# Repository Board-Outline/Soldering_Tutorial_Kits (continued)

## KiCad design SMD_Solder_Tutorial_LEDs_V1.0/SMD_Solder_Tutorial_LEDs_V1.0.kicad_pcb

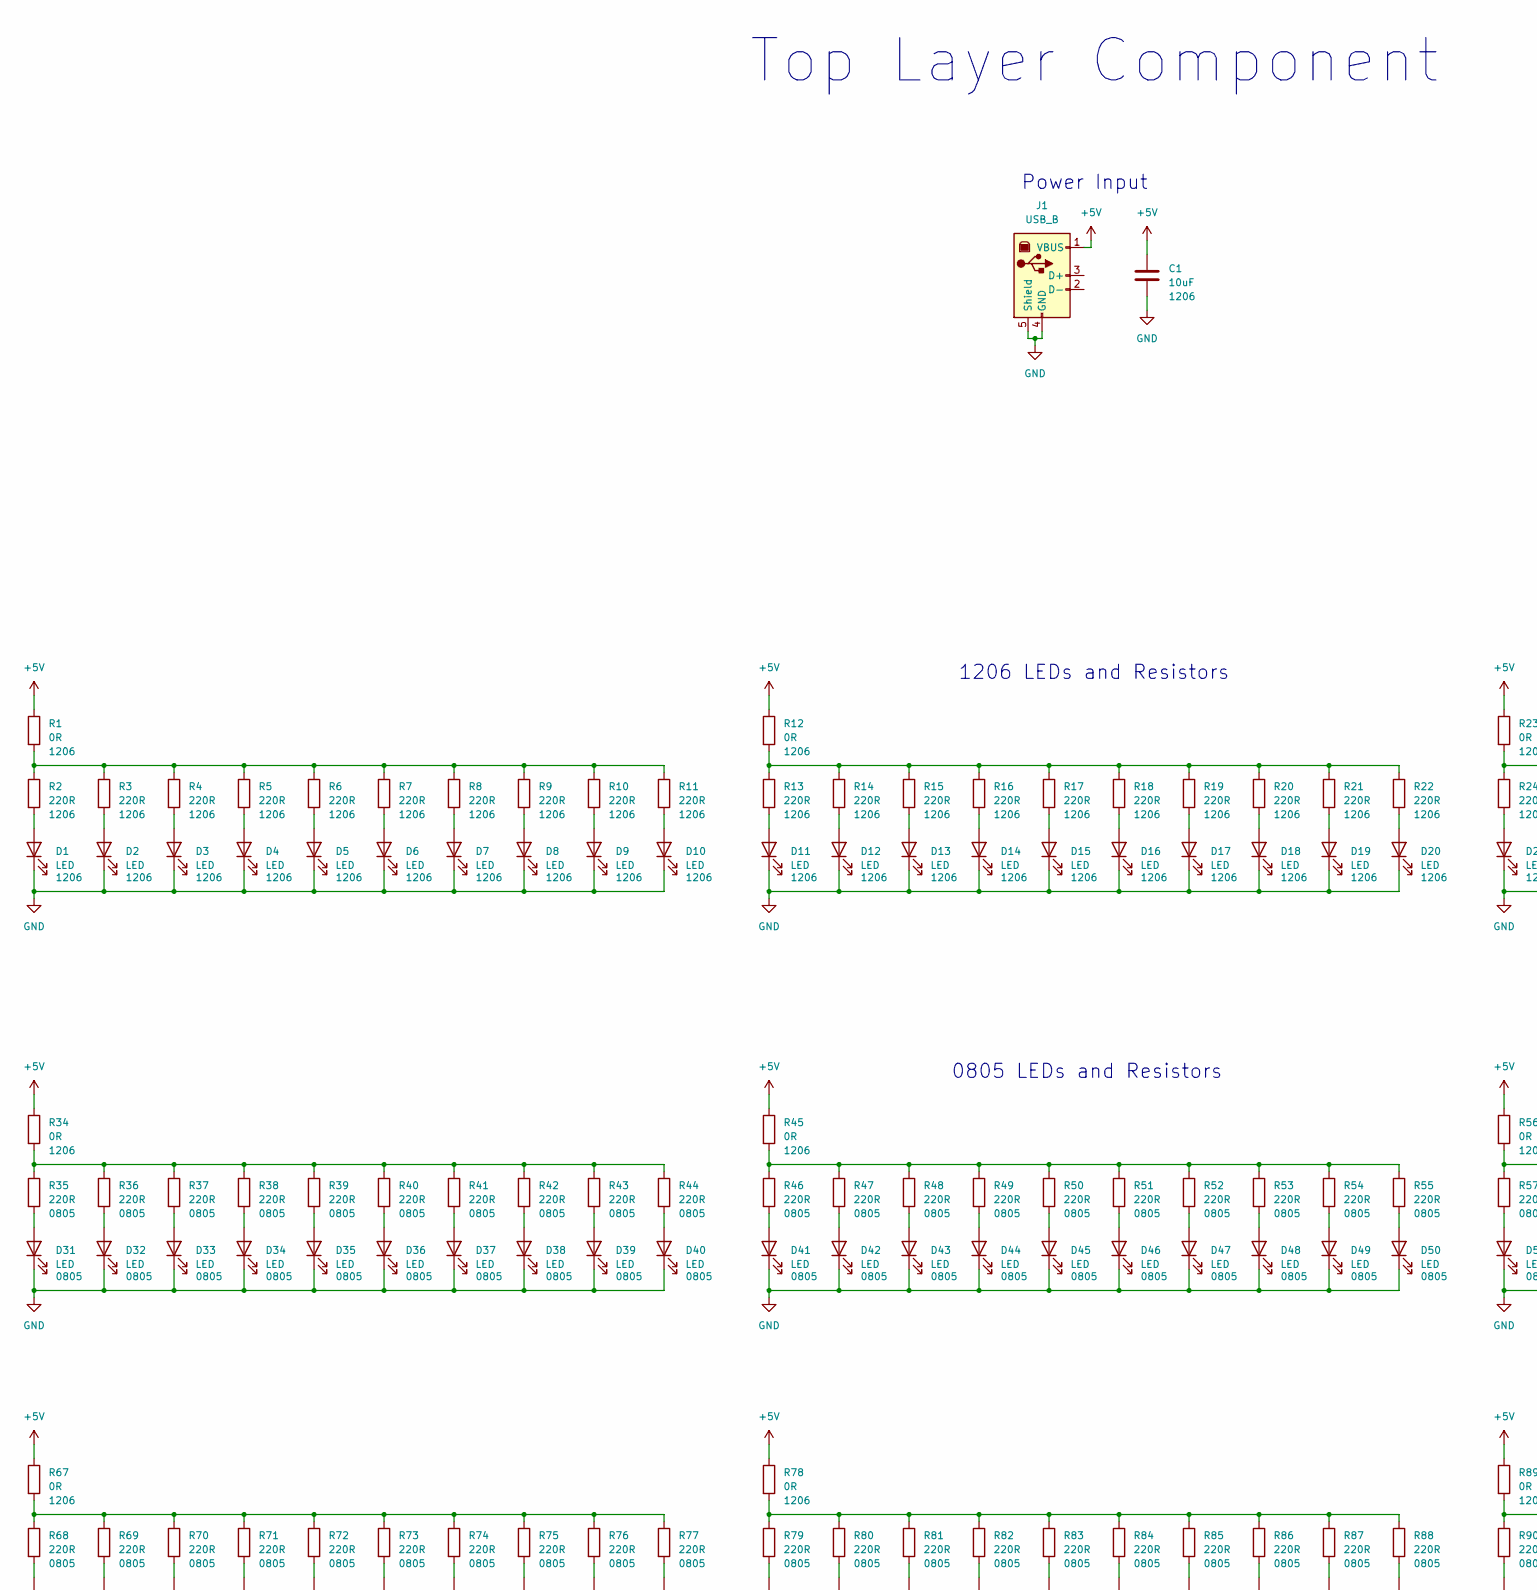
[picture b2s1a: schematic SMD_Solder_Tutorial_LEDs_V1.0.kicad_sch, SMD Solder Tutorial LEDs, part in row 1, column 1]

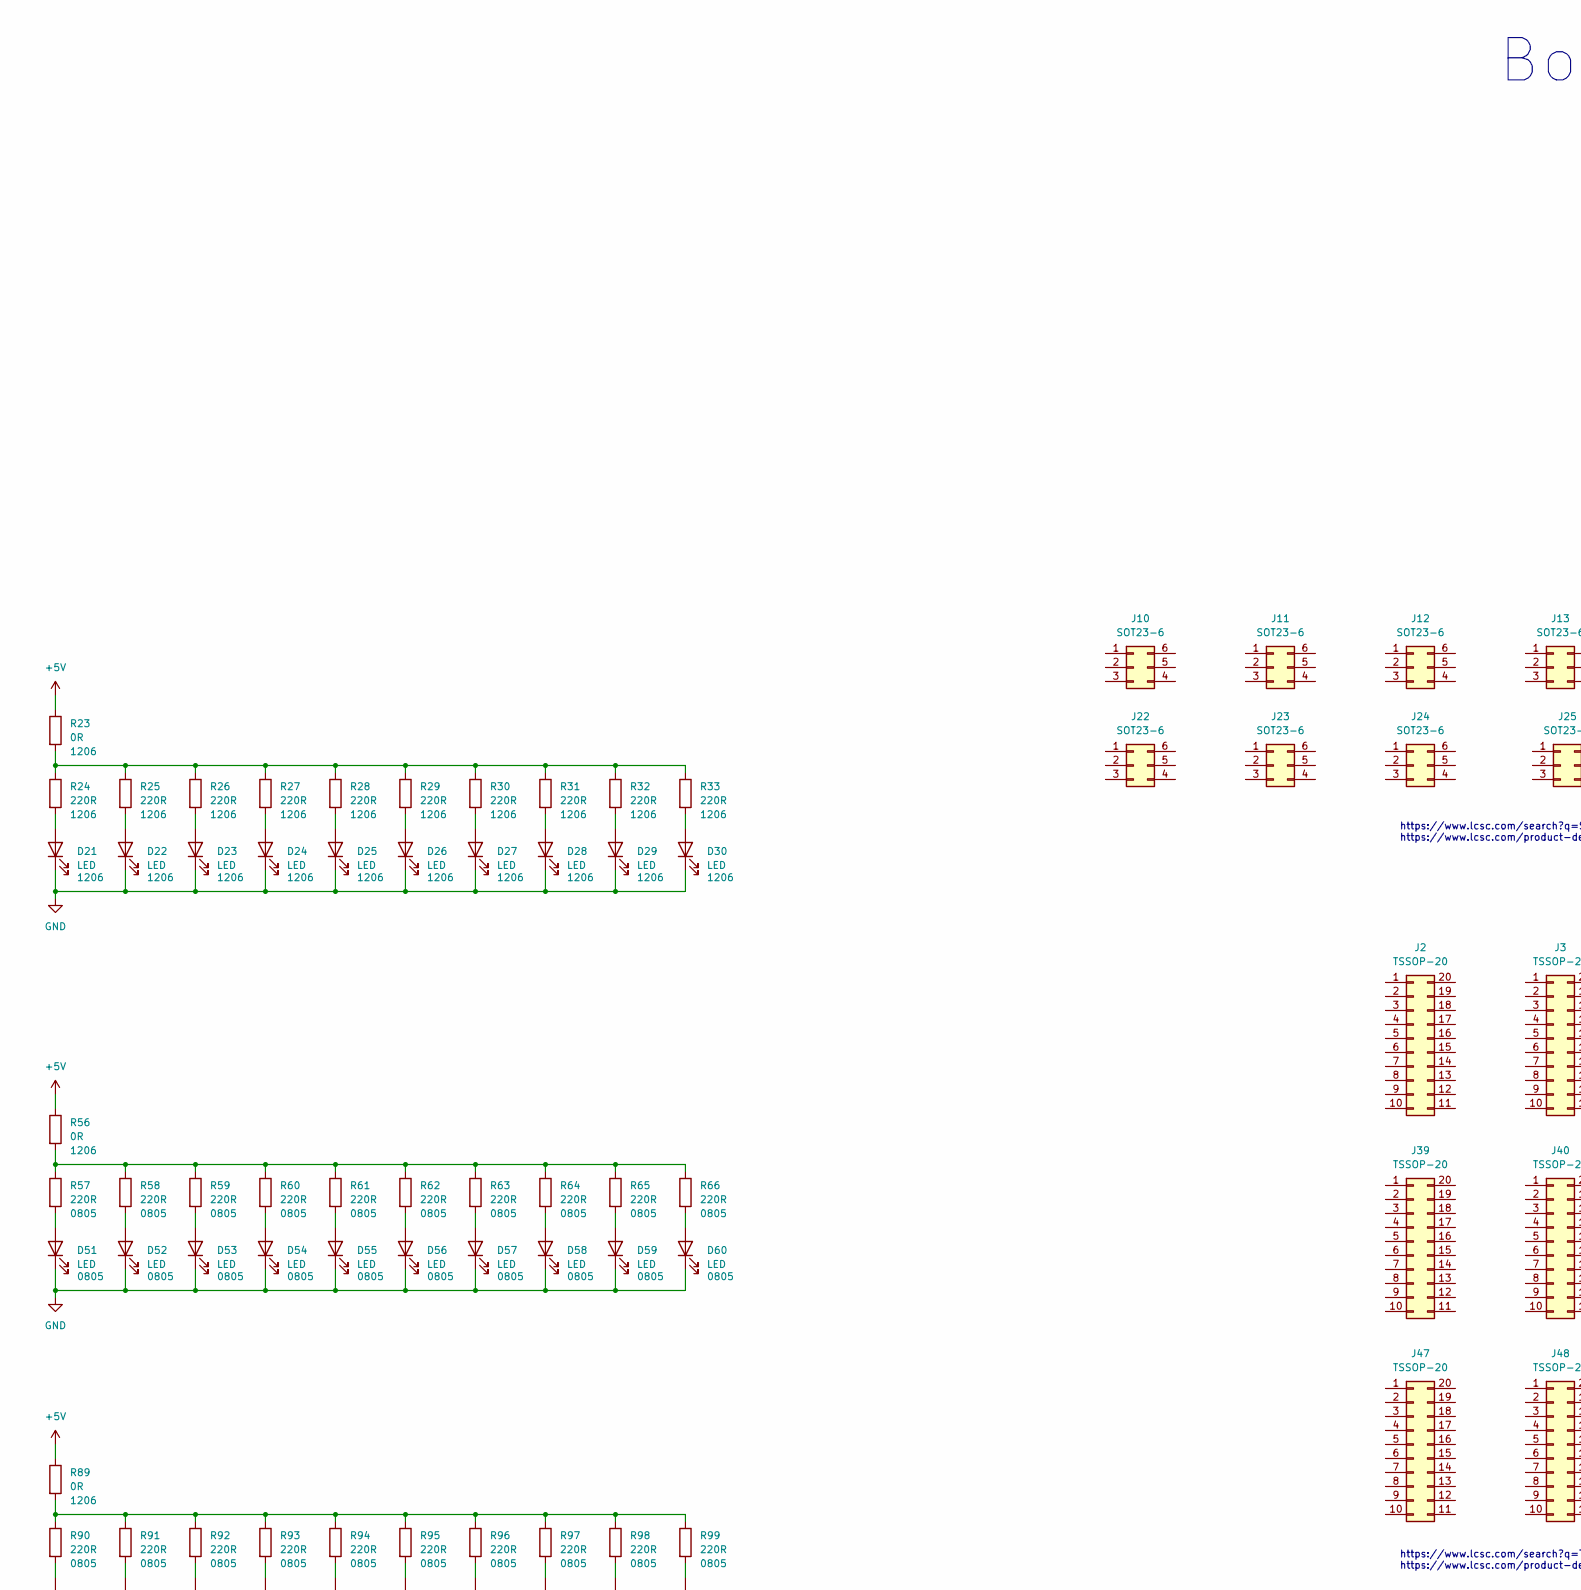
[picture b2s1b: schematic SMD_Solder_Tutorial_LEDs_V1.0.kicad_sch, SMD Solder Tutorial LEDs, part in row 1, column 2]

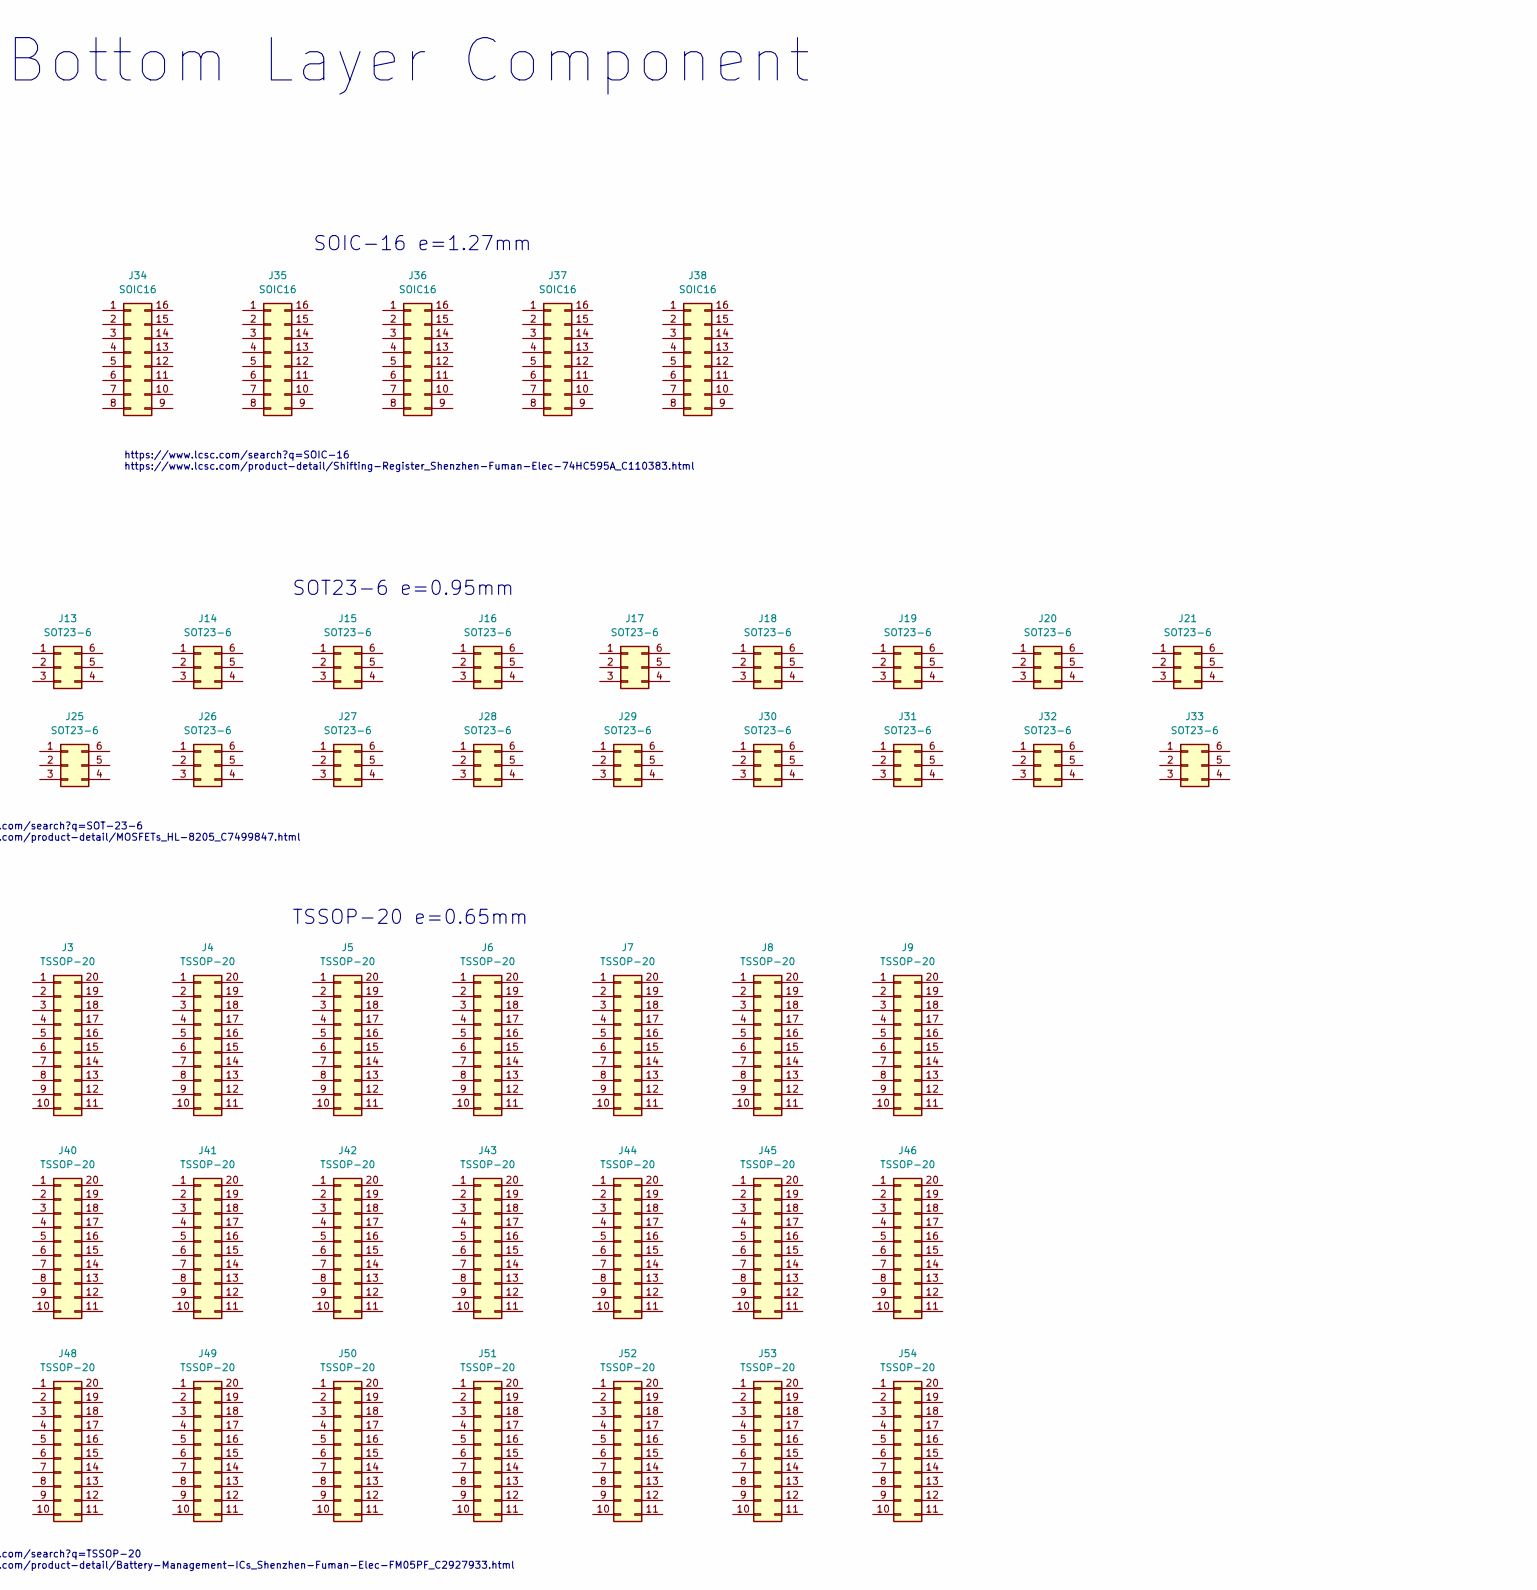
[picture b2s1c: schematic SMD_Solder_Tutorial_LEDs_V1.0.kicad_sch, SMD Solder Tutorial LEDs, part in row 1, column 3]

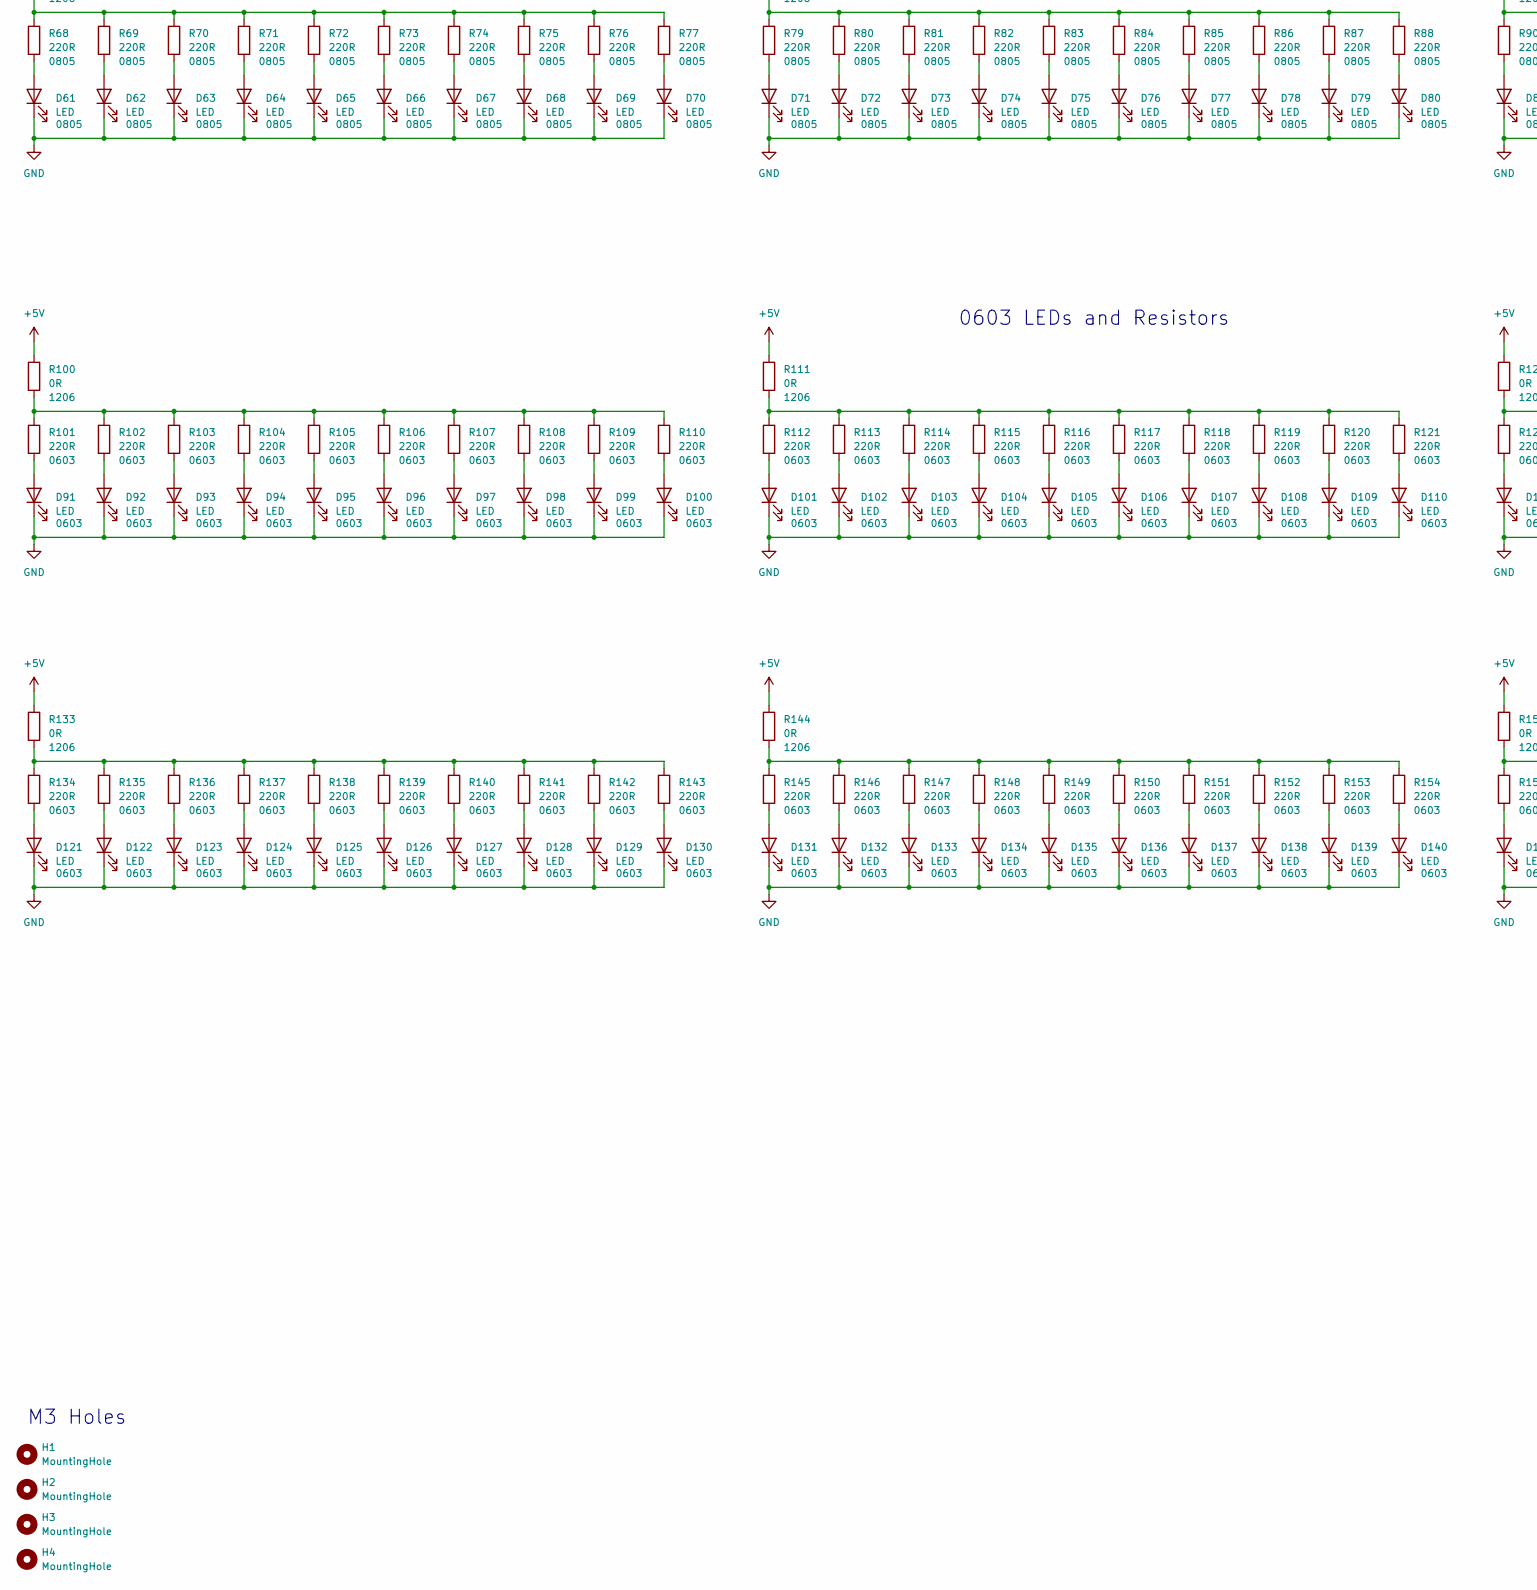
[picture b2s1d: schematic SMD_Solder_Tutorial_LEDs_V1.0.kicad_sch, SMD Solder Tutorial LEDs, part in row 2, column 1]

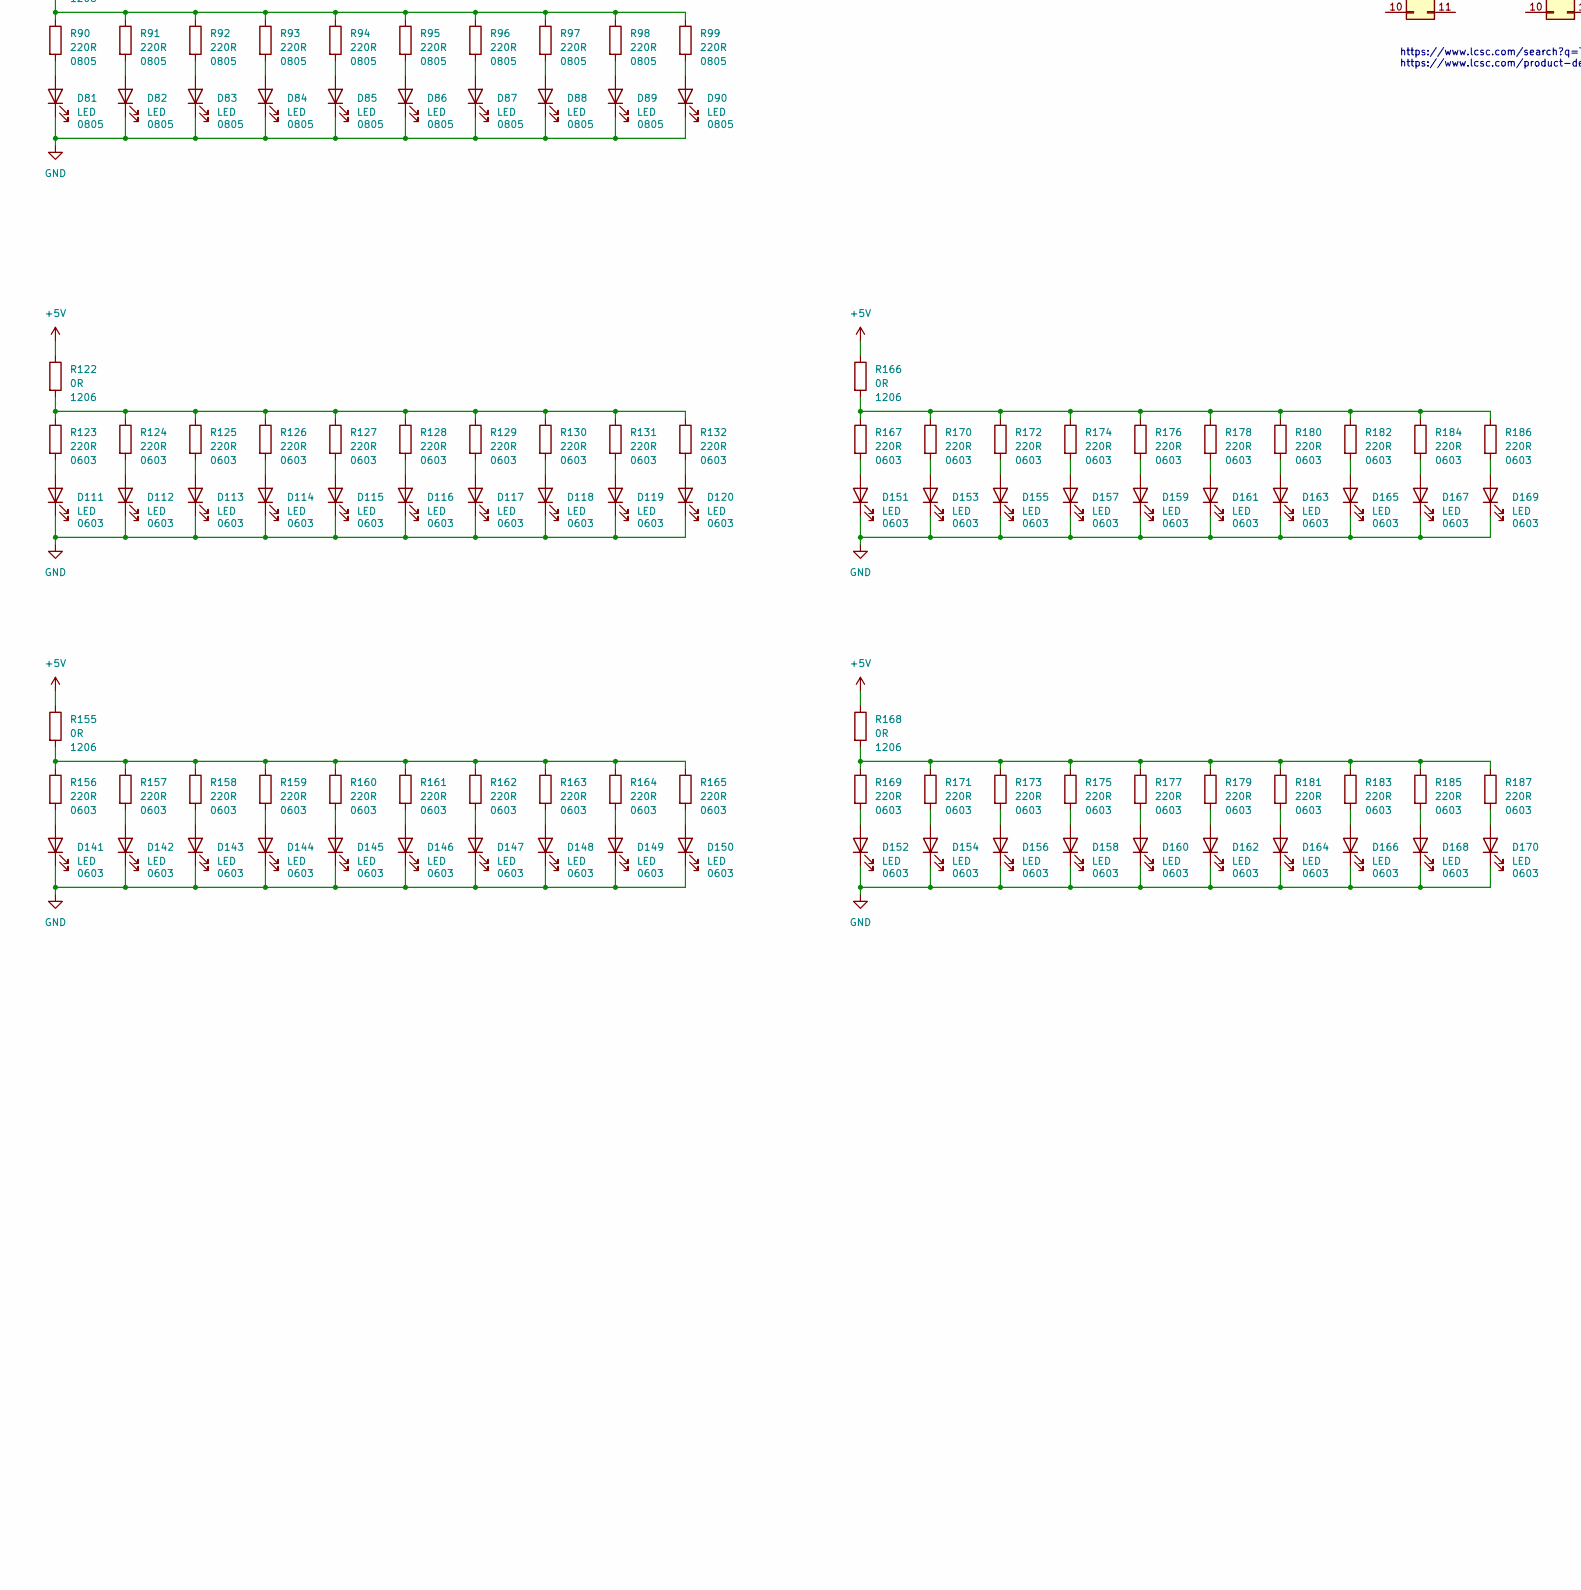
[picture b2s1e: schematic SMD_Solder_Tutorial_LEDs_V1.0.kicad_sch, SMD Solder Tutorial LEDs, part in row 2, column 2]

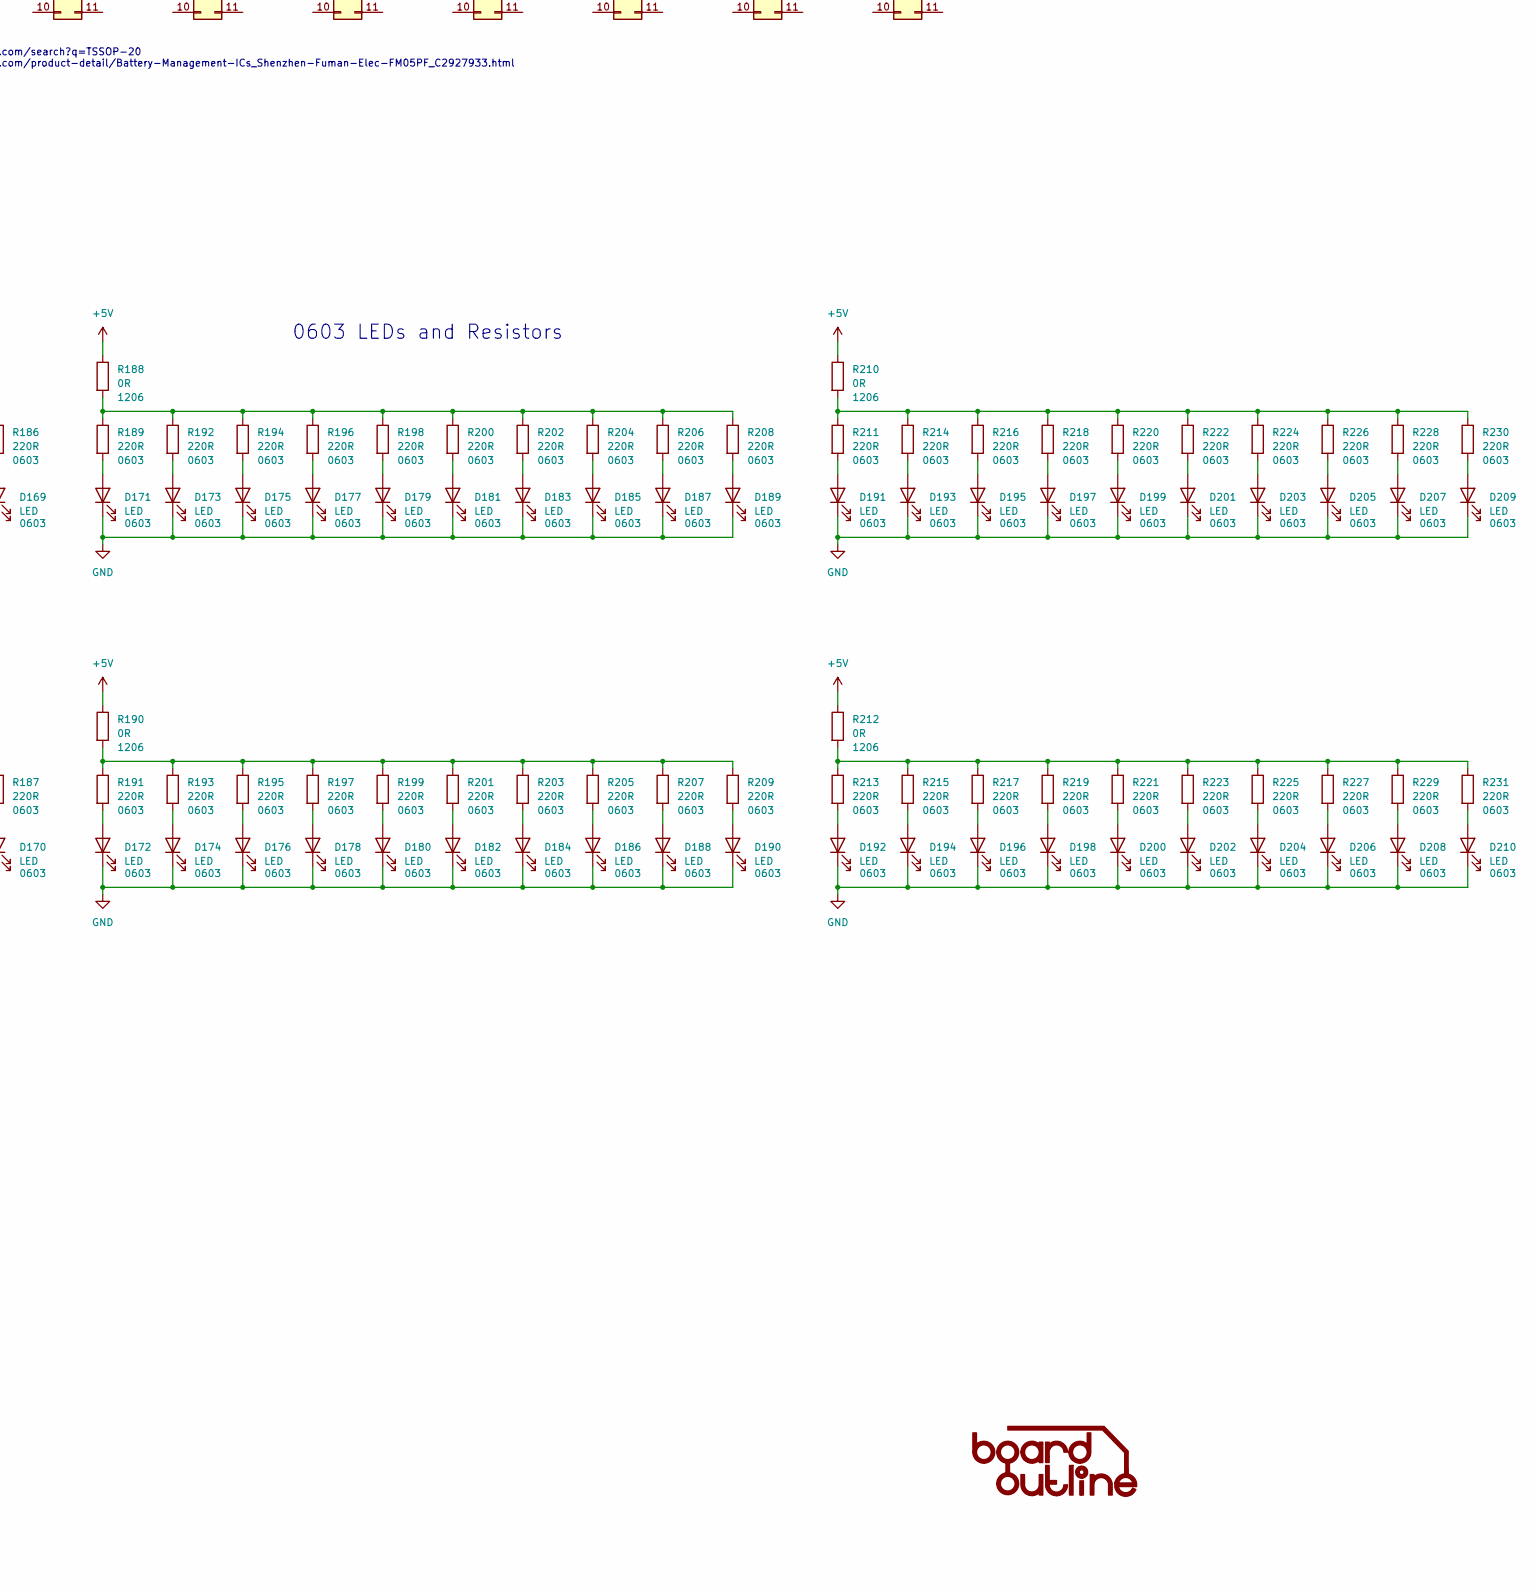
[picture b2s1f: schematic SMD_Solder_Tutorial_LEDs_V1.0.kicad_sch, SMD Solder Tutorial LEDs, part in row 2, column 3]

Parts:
C1: 10uF; C_1206_3216Metric_Pad1.33x1.80mm_HandSolder
D1, D2, D3, D4, D5, D6, D7, D8, D9, D10, D11, D12, D13, D14, D15, D16, D17, D18, D19, D20, D21, D22, D23, D24, D25, D26, D27, D28, D29, D30: LED; LED_1206_3216Metric_Pad1.42x1.75mm_HandSolder; Manufacturer Part Number XL-3216UGC
D31, D32, D33, D34, D35, D36, D37, D38, D39, D40, D41, D42, D43, D44, D45, D46, D47, D48, D49, D50, D51, D52, D53, D54, D55, D56, D57, D58, D59, D60, D61, D62, D63, D64, D65, D66, D67, D68, D69, D70, D71, D72, D73, D74, D75, D76, D77, D78, D79, D80, D81, D82, D83, D84, D85, D86, D87, D88, D89, D90: LED; LED_0805_2012Metric_Pad1.15x1.40mm_HandSolder; Manufacturer Part Number XL-2012UGC
D91, D92, D93, D94, D95, D96, D97, D98, D99, D100, D101, D102, D103, D104, D105, D106, D107, D108, D109, D110, D111, D112, D113, D114, D115, D116, D117, D118, D119, D120, D121, D122, D123, D124, D125, D126, D127, D128, D129, D130, D131, D132, D133, D134, D135, D136, D137, D138, D139, D140, D141, D142, D143, D144, D145, D146, D147, D148, D149, D150, D151, D152, D153, D154, D155, D156, D157, D158, D159, D160, D161, D162, D163, D164, D165, D166, D167, D168, D169, D170, D171, D172, D173, D174, D175, D176, D177, D178, D179, D180, D181, D182, D183, D184, D185, D186, D187, D188, D189, D190, D191, D192, D193, D194, D195, D196, D197, D198, D199, D200, D201, D202, D203, D204, D205, D206, D207, D208, D209, D210: LED; LED_0603_1608Metric_Pad1.05x0.95mm_HandSolder; Manufacturer Part Number XL-1608UGC-04
H1, H2, H3, H4: MountingHole; MountingHole_3.2mm_M3_DIN965
J1: USB_B; USB_B_OST_USB-B1HSxx_Horizontal; Manufacturer Part Number USB-B10-BRW
J2, J3, J4, J5, J6, J7, J8, J9, J39, J40, J41, J42, J43, J44, J45, J46, J47, J48, J49, J50, J51, J52, J53, J54: TSSOP-20; TSSOP-20_4.4x6.5mm_P0.65mm; Manufacturer Part Number FM05PF
J10, J11, J12, J13, J14, J15, J16, J17, J18, J19, J20, J21, J22, J23, J24, J25, J26, J27, J28, J29, J30, J31, J32, J33: SOT23-6; SOT-23-6_Handsoldering
J34, J35, J36, J37, J38: SOIC16; SOIC-16W_5.3x10.2mm_P1.27mm; Manufacturer Part Number C7499847
R1, R12, R23, R34, R45, R56, R67, R78, R89, R100, R111, R122, R133, R144, R155, R166, R168, R188, R190, R210, R212: 0R; R_1206_3216Metric_Pad1.30x1.75mm_HandSolder
R2, R3, R4, R5, R6, R7, R8, R9, R10, R11, R13, R14, R15, R16, R17, R18, R19, R20, R21, R22, R24, R25, R26, R27, R28, R29, R30, R31, R32, R33: 220R; R_1206_3216Metric_Pad1.30x1.75mm_HandSolder
R35, R36, R37, R38, R39, R40, R41, R42, R43, R44, R46, R47, R48, R49, R50, R51, R52, R53, R54, R55, R57, R58, R59, R60, R61, R62, R63, R64, R65, R66, R68, R69, R70, R71, R72, R73, R74, R75, R76, R77, R79, R80, R81, R82, R83, R84, R85, R86, R87, R88, R90, R91, R92, R93, R94, R95, R96, R97, R98, R99: 220R; R_0805_2012Metric_Pad1.20x1.40mm_HandSolder
R101, R102, R103, R104, R105, R106, R107, R108, R109, R110, R112, R113, R114, R115, R116, R117, R118, R119, R120, R121, R123, R124, R125, R126, R127, R128, R129, R130, R131, R132, R134, R135, R136, R137, R138, R139, R140, R141, R142, R143, R145, R146, R147, R148, R149, R150, R151, R152, R153, R154, R156, R157, R158, R159, R160, R161, R162, R163, R164, R165, R167, R169, R170, R171, R172, R173, R174, R175, R176, R177, R178, R179, R180, R181, R182, R183, R184, R185, R186, R187, R189, R191, R192, R193, R194, R195, R196, R197, R198, R199, R200, R201, R202, R203, R204, R205, R206, R207, R208, R209, R211, R213, R214, R215, R216, R217, R218, R219, R220, R221, R222, R223, R224, R225, R226, R227, R228, R229, R230, R231: 220R; R_0603_1608Metric_Pad0.98x0.95mm_HandSolder

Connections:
+5V: C1.1, J1.1 (VBUS), R1.1, R12.1, R23.1, R34.1, R45.1, R56.1, R67.1, R78.1, R89.1, R100.1, R111.1, R122.1, R133.1, R144.1, R155.1, R166.1, R168.1, R188.1, R190.1, R210.1, R212.1
GND: C1.2, D1.1 (K), D2.1 (K), D3.1 (K), D4.1 (K), D5.1 (K), D6.1 (K), D7.1 (K), D8.1 (K), D9.1 (K), D10.1 (K), D11.1 (K), D12.1 (K), D13.1 (K), D14.1 (K), D15.1 (K), D16.1 (K), D17.1 (K), D18.1 (K), D19.1 (K), D20.1 (K), D21.1 (K), D22.1 (K), D23.1 (K), D24.1 (K), D25.1 (K), D26.1 (K), D27.1 (K), D28.1 (K), D29.1 (K), D30.1 (K), D31.1 (K), D32.1 (K), D33.1 (K), D34.1 (K), D35.1 (K), D36.1 (K), D37.1 (K), D38.1 (K), D39.1 (K), D40.1 (K), D41.1 (K), D42.1 (K), D43.1 (K), D44.1 (K), D45.1 (K), D46.1 (K), D47.1 (K), D48.1 (K), D49.1 (K), D50.1 (K), D51.1 (K), D52.1 (K), D53.1 (K), D54.1 (K), D55.1 (K), D56.1 (K), D57.1 (K), D58.1 (K), D59.1 (K), D60.1 (K), D61.1 (K), D62.1 (K), D63.1 (K), D64.1 (K), D65.1 (K), D66.1 (K), D67.1 (K), D68.1 (K), D69.1 (K), D70.1 (K), D71.1 (K), D72.1 (K), D73.1 (K), D74.1 (K), D75.1 (K), D76.1 (K), D77.1 (K), D78.1 (K), D79.1 (K), D80.1 (K), D81.1 (K), D82.1 (K), D83.1 (K), D84.1 (K), D85.1 (K), D86.1 (K), D87.1 (K), D88.1 (K), D89.1 (K), D90.1 (K), D91.1 (K), D92.1 (K), D93.1 (K), D94.1 (K), D95.1 (K), D96.1 (K), D97.1 (K), D98.1 (K), D99.1 (K), D100.1 (K), D101.1 (K), D102.1 (K), D103.1 (K), D104.1 (K), D105.1 (K), D106.1 (K), D107.1 (K), D108.1 (K), D109.1 (K), D110.1 (K), D111.1 (K), D112.1 (K), D113.1 (K), D114.1 (K), D115.1 (K), D116.1 (K), D117.1 (K), D118.1 (K), D119.1 (K), D120.1 (K), D121.1 (K), D122.1 (K), D123.1 (K), D124.1 (K), D125.1 (K), D126.1 (K), D127.1 (K), D128.1 (K), D129.1 (K), D130.1 (K), D131.1 (K), D132.1 (K), D133.1 (K), D134.1 (K), D135.1 (K), D136.1 (K), D137.1 (K), D138.1 (K), D139.1 (K), D140.1 (K), D141.1 (K), D142.1 (K), D143.1 (K), D144.1 (K), D145.1 (K), D146.1 (K), D147.1 (K), D148.1 (K), D149.1 (K), D150.1 (K), D151.1 (K), D152.1 (K), D153.1 (K), D154.1 (K), D155.1 (K), D156.1 (K), D157.1 (K), D158.1 (K), D159.1 (K), D160.1 (K), D161.1 (K), D162.1 (K), D163.1 (K), D164.1 (K), D165.1 (K), D166.1 (K), D167.1 (K), D168.1 (K), D169.1 (K), D170.1 (K), D171.1 (K), D172.1 (K), D173.1 (K), D174.1 (K), D175.1 (K), D176.1 (K), D177.1 (K), D178.1 (K), D179.1 (K), D180.1 (K), D181.1 (K), D182.1 (K), D183.1 (K), D184.1 (K), D185.1 (K), D186.1 (K), D187.1 (K), D188.1 (K), D189.1 (K), D190.1 (K), D191.1 (K), D192.1 (K), D193.1 (K), D194.1 (K), D195.1 (K), D196.1 (K), D197.1 (K), D198.1 (K), D199.1 (K), D200.1 (K), D201.1 (K), D202.1 (K), D203.1 (K), D204.1 (K), D205.1 (K), D206.1 (K), D207.1 (K), D208.1 (K), D209.1 (K), D210.1 (K), J1.4 (GND), J1.5 (Shield)
unnamed: D1.2 (A), R2.2
unnamed: D2.2 (A), R3.2
unnamed: D3.2 (A), R4.2
unnamed: D4.2 (A), R5.2
unnamed: D5.2 (A), R6.2
unnamed: D6.2 (A), R7.2
unnamed: D7.2 (A), R8.2
unnamed: D8.2 (A), R9.2
unnamed: D9.2 (A), R10.2
unnamed: D10.2 (A), R11.2
unnamed: D11.2 (A), R13.2
unnamed: D12.2 (A), R14.2
unnamed: D13.2 (A), R15.2
unnamed: D14.2 (A), R16.2
unnamed: D15.2 (A), R17.2
unnamed: D16.2 (A), R18.2
unnamed: D17.2 (A), R19.2
unnamed: D18.2 (A), R20.2
unnamed: D19.2 (A), R21.2
unnamed: D20.2 (A), R22.2
unnamed: D21.2 (A), R24.2
unnamed: D22.2 (A), R25.2
unnamed: D23.2 (A), R26.2
unnamed: D24.2 (A), R27.2
unnamed: D25.2 (A), R28.2
unnamed: D26.2 (A), R29.2
unnamed: D27.2 (A), R30.2
unnamed: D28.2 (A), R31.2
unnamed: D29.2 (A), R32.2
unnamed: D30.2 (A), R33.2
unnamed: D31.2 (A), R35.2
unnamed: D32.2 (A), R36.2
unnamed: D33.2 (A), R37.2
unnamed: D34.2 (A), R38.2
unnamed: D35.2 (A), R39.2
unnamed: D36.2 (A), R40.2
unnamed: D37.2 (A), R41.2
unnamed: D38.2 (A), R42.2
unnamed: D39.2 (A), R43.2
unnamed: D40.2 (A), R44.2
unnamed: D41.2 (A), R46.2
unnamed: D42.2 (A), R47.2
unnamed: D43.2 (A), R48.2
unnamed: D44.2 (A), R49.2
unnamed: D45.2 (A), R50.2
unnamed: D46.2 (A), R51.2
unnamed: D47.2 (A), R52.2
unnamed: D48.2 (A), R53.2
unnamed: D49.2 (A), R54.2
unnamed: D50.2 (A), R55.2
unnamed: D51.2 (A), R57.2
unnamed: D52.2 (A), R58.2
unnamed: D53.2 (A), R59.2
unnamed: D54.2 (A), R60.2
unnamed: D55.2 (A), R61.2
unnamed: D56.2 (A), R62.2
unnamed: D57.2 (A), R63.2
unnamed: D58.2 (A), R64.2
unnamed: D59.2 (A), R65.2
unnamed: D60.2 (A), R66.2
unnamed: D61.2 (A), R68.2
unnamed: D62.2 (A), R69.2
unnamed: D63.2 (A), R70.2
unnamed: D64.2 (A), R71.2
unnamed: D65.2 (A), R72.2
unnamed: D66.2 (A), R73.2
unnamed: D67.2 (A), R74.2
unnamed: D68.2 (A), R75.2
unnamed: D69.2 (A), R76.2
unnamed: D70.2 (A), R77.2
unnamed: D71.2 (A), R79.2
unnamed: D72.2 (A), R80.2
unnamed: D73.2 (A), R81.2
unnamed: D74.2 (A), R82.2
unnamed: D75.2 (A), R83.2
unnamed: D76.2 (A), R84.2
unnamed: D77.2 (A), R85.2
unnamed: D78.2 (A), R86.2
unnamed: D79.2 (A), R87.2
unnamed: D80.2 (A), R88.2
unnamed: D81.2 (A), R90.2
unnamed: D82.2 (A), R91.2
unnamed: D83.2 (A), R92.2
unnamed: D84.2 (A), R93.2
unnamed: D85.2 (A), R94.2
unnamed: D86.2 (A), R95.2
unnamed: D87.2 (A), R96.2
unnamed: D88.2 (A), R97.2
unnamed: D89.2 (A), R98.2
unnamed: D90.2 (A), R99.2
unnamed: D91.2 (A), R101.2
unnamed: D92.2 (A), R102.2
unnamed: D93.2 (A), R103.2
unnamed: D94.2 (A), R104.2
unnamed: D95.2 (A), R105.2
unnamed: D96.2 (A), R106.2
unnamed: D97.2 (A), R107.2
unnamed: D98.2 (A), R108.2
unnamed: D99.2 (A), R109.2
unnamed: D100.2 (A), R110.2
unnamed: D101.2 (A), R112.2
unnamed: D102.2 (A), R113.2
unnamed: D103.2 (A), R114.2
unnamed: D104.2 (A), R115.2
unnamed: D105.2 (A), R116.2
unnamed: D106.2 (A), R117.2
unnamed: D107.2 (A), R118.2
unnamed: D108.2 (A), R119.2
unnamed: D109.2 (A), R120.2
unnamed: D110.2 (A), R121.2
unnamed: D111.2 (A), R123.2
unnamed: D112.2 (A), R124.2
unnamed: D113.2 (A), R125.2
unnamed: D114.2 (A), R126.2
unnamed: D115.2 (A), R127.2
unnamed: D116.2 (A), R128.2
unnamed: D117.2 (A), R129.2
unnamed: D118.2 (A), R130.2
unnamed: D119.2 (A), R131.2
unnamed: D120.2 (A), R132.2
unnamed: D121.2 (A), R134.2
unnamed: D122.2 (A), R135.2
unnamed: D123.2 (A), R136.2
unnamed: D124.2 (A), R137.2
unnamed: D125.2 (A), R138.2
unnamed: D126.2 (A), R139.2
unnamed: D127.2 (A), R140.2
unnamed: D128.2 (A), R141.2
unnamed: D129.2 (A), R142.2
unnamed: D130.2 (A), R143.2
unnamed: D131.2 (A), R145.2
unnamed: D132.2 (A), R146.2
unnamed: D133.2 (A), R147.2
unnamed: D134.2 (A), R148.2
unnamed: D135.2 (A), R149.2
unnamed: D136.2 (A), R150.2
unnamed: D137.2 (A), R151.2
unnamed: D138.2 (A), R152.2
unnamed: D139.2 (A), R153.2
unnamed: D140.2 (A), R154.2
unnamed: D141.2 (A), R156.2
unnamed: D142.2 (A), R157.2
unnamed: D143.2 (A), R158.2
unnamed: D144.2 (A), R159.2
unnamed: D145.2 (A), R160.2
unnamed: D146.2 (A), R161.2
unnamed: D147.2 (A), R162.2
unnamed: D148.2 (A), R163.2
unnamed: D149.2 (A), R164.2
unnamed: D150.2 (A), R165.2
unnamed: D151.2 (A), R167.2
unnamed: D152.2 (A), R169.2
unnamed: D153.2 (A), R170.2
unnamed: D154.2 (A), R171.2
unnamed: D155.2 (A), R172.2
unnamed: D156.2 (A), R173.2
unnamed: D157.2 (A), R174.2
unnamed: D158.2 (A), R175.2
unnamed: D159.2 (A), R176.2
unnamed: D160.2 (A), R177.2
unnamed: D161.2 (A), R178.2
unnamed: D162.2 (A), R179.2
unnamed: D163.2 (A), R180.2
unnamed: D164.2 (A), R181.2
unnamed: D165.2 (A), R182.2
unnamed: D166.2 (A), R183.2
unnamed: D167.2 (A), R184.2
unnamed: D168.2 (A), R185.2
unnamed: D169.2 (A), R186.2
unnamed: D170.2 (A), R187.2
unnamed: D171.2 (A), R189.2
unnamed: D172.2 (A), R191.2
unnamed: D173.2 (A), R192.2
unnamed: D174.2 (A), R193.2
unnamed: D175.2 (A), R194.2
unnamed: D176.2 (A), R195.2
unnamed: D177.2 (A), R196.2
unnamed: D178.2 (A), R197.2
unnamed: D179.2 (A), R198.2
unnamed: D180.2 (A), R199.2
unnamed: D181.2 (A), R200.2
unnamed: D182.2 (A), R201.2
unnamed: D183.2 (A), R202.2
unnamed: D184.2 (A), R203.2
unnamed: D185.2 (A), R204.2
unnamed: D186.2 (A), R205.2
unnamed: D187.2 (A), R206.2
unnamed: D188.2 (A), R207.2
unnamed: D189.2 (A), R208.2
unnamed: D190.2 (A), R209.2
unnamed: D191.2 (A), R211.2
unnamed: D192.2 (A), R213.2
unnamed: D193.2 (A), R214.2
unnamed: D194.2 (A), R215.2
unnamed: D195.2 (A), R216.2
unnamed: D196.2 (A), R217.2
unnamed: D197.2 (A), R218.2
unnamed: D198.2 (A), R219.2
unnamed: D199.2 (A), R220.2
unnamed: D200.2 (A), R221.2
unnamed: D201.2 (A), R222.2
unnamed: D202.2 (A), R223.2
unnamed: D203.2 (A), R224.2
unnamed: D204.2 (A), R225.2
unnamed: D205.2 (A), R226.2
unnamed: D206.2 (A), R227.2
unnamed: D207.2 (A), R228.2
unnamed: D208.2 (A), R229.2
unnamed: D209.2 (A), R230.2
unnamed: D210.2 (A), R231.2
unnamed: R1.2, R2.1, R3.1, R4.1, R5.1, R6.1, R7.1, R8.1, R9.1, R10.1, R11.1
unnamed: R12.2, R13.1, R14.1, R15.1, R16.1, R17.1, R18.1, R19.1, R20.1, R21.1, R22.1
unnamed: R23.2, R24.1, R25.1, R26.1, R27.1, R28.1, R29.1, R30.1, R31.1, R32.1, R33.1
unnamed: R34.2, R35.1, R36.1, R37.1, R38.1, R39.1, R40.1, R41.1, R42.1, R43.1, R44.1
unnamed: R45.2, R46.1, R47.1, R48.1, R49.1, R50.1, R51.1, R52.1, R53.1, R54.1, R55.1
unnamed: R56.2, R57.1, R58.1, R59.1, R60.1, R61.1, R62.1, R63.1, R64.1, R65.1, R66.1
unnamed: R67.2, R68.1, R69.1, R70.1, R71.1, R72.1, R73.1, R74.1, R75.1, R76.1, R77.1
unnamed: R78.2, R79.1, R80.1, R81.1, R82.1, R83.1, R84.1, R85.1, R86.1, R87.1, R88.1
unnamed: R89.2, R90.1, R91.1, R92.1, R93.1, R94.1, R95.1, R96.1, R97.1, R98.1, R99.1
unnamed: R100.2, R101.1, R102.1, R103.1, R104.1, R105.1, R106.1, R107.1, R108.1, R109.1, R110.1
unnamed: R111.2, R112.1, R113.1, R114.1, R115.1, R116.1, R117.1, R118.1, R119.1, R120.1, R121.1
unnamed: R122.2, R123.1, R124.1, R125.1, R126.1, R127.1, R128.1, R129.1, R130.1, R131.1, R132.1
unnamed: R133.2, R134.1, R135.1, R136.1, R137.1, R138.1, R139.1, R140.1, R141.1, R142.1, R143.1
unnamed: R144.2, R145.1, R146.1, R147.1, R148.1, R149.1, R150.1, R151.1, R152.1, R153.1, R154.1
unnamed: R155.2, R156.1, R157.1, R158.1, R159.1, R160.1, R161.1, R162.1, R163.1, R164.1, R165.1
unnamed: R166.2, R167.1, R170.1, R172.1, R174.1, R176.1, R178.1, R180.1, R182.1, R184.1, R186.1
unnamed: R168.2, R169.1, R171.1, R173.1, R175.1, R177.1, R179.1, R181.1, R183.1, R185.1, R187.1
unnamed: R188.2, R189.1, R192.1, R194.1, R196.1, R198.1, R200.1, R202.1, R204.1, R206.1, R208.1
unnamed: R190.2, R191.1, R193.1, R195.1, R197.1, R199.1, R201.1, R203.1, R205.1, R207.1, R209.1
unnamed: R210.2, R211.1, R214.1, R216.1, R218.1, R220.1, R222.1, R224.1, R226.1, R228.1, R230.1
unnamed: R212.2, R213.1, R215.1, R217.1, R219.1, R221.1, R223.1, R225.1, R227.1, R229.1, R231.1

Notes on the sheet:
M3 Holes
https://www.lcsc.com/search?q=TSSOP-20 https://www.lcsc.com/product-detail/Battery-Management-ICs_Shenzhen-Fuman-Elec-FM05PF_C2927933.html
https://www.lcsc.com/search?q=SOT-23-6 https://www.lcsc.com/product-detail/MOSFETs_HL-8205_C7499847.html
Power Input
TSSOP-20 e=0.65mm
0603 LEDs and Resistors
Bottom Layer Component
SOT23-6 e=0.95mm
0805 LEDs and Resistors
Top Layer Component
https://www.lcsc.com/search?q=SOIC-16 https://www.lcsc.com/product-detail/Shifting-Register_Shenzhen-Fuman-Elec-74HC595A_C110383.html
SOIC-16 e=1.27mm
1206 LEDs and Resistors
